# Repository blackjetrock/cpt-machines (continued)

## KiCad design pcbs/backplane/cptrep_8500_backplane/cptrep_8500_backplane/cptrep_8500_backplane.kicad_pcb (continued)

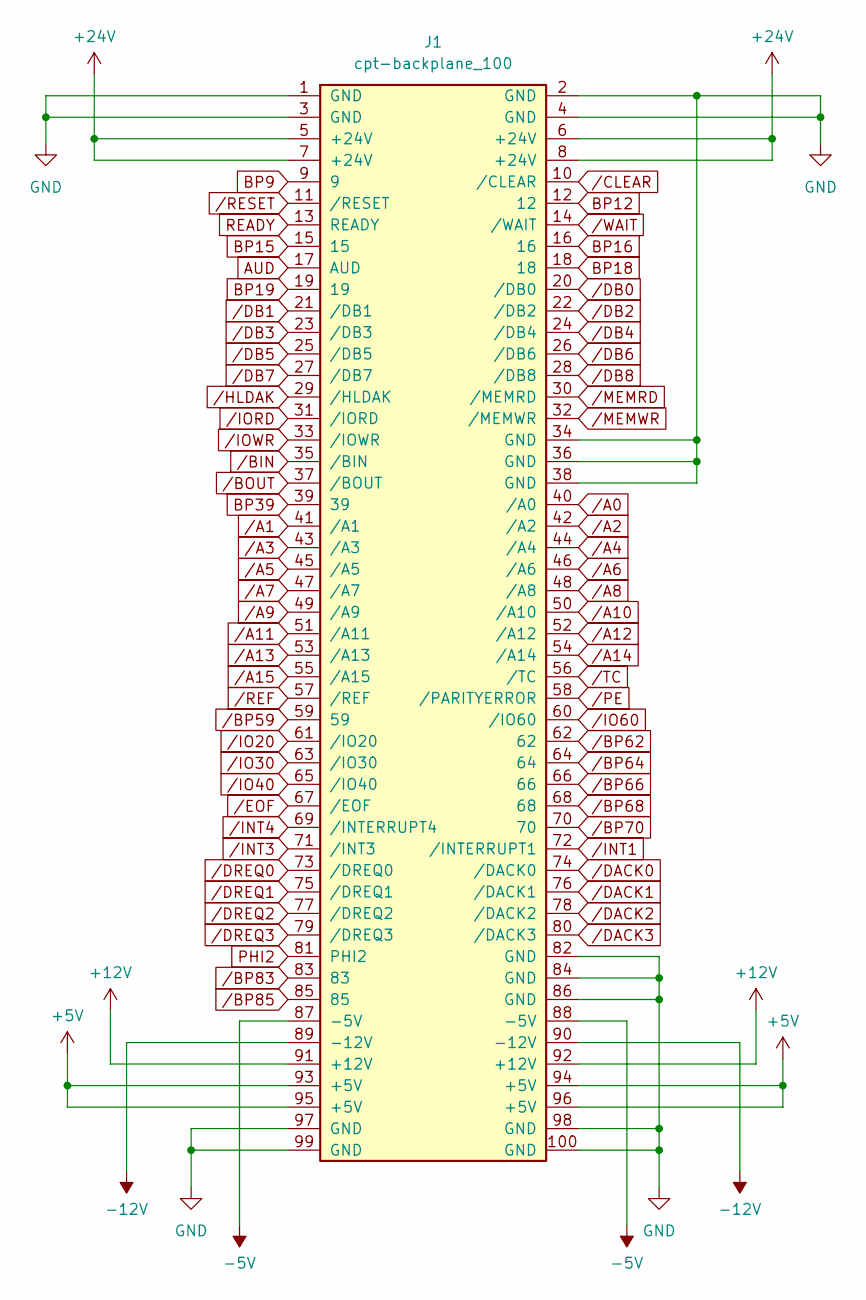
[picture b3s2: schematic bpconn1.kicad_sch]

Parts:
J1: cpt-backplane_100; cpt-8500-backplane-connector

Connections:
+5V: J1.93 (+5V), J1.94 (+5V), J1.95 (+5V), J1.96 (+5V); also elsewhere on the board
+12V: J1.91 (+12V), J1.92 (+12V); also elsewhere on the board
+24V: J1.5 (+24V), J1.6 (+24V), J1.7 (+24V), J1.8 (+24V); also elsewhere on the board
-5V: J1.87 (-5V), J1.88 (-5V); also elsewhere on the board
-12V: J1.89 (-12V), J1.90 (-12V); also elsewhere on the board
AUD: J1.17 (AUD); also elsewhere on the board
BP9: J1.9; also elsewhere on the board
BP12: J1.12; also elsewhere on the board
BP15: J1.15; also elsewhere on the board
BP16: J1.16; also elsewhere on the board
BP18: J1.18; also elsewhere on the board
BP19: J1.19; also elsewhere on the board
BP39: J1.39; also elsewhere on the board
GND: J1.1 (GND), J1.2 (GND), J1.3 (GND), J1.4 (GND), J1.34 (GND), J1.36 (GND), J1.38 (GND), J1.82 (GND), J1.84 (GND), J1.86 (GND), J1.97 (GND), J1.98 (GND), J1.99 (GND), J1.100 (GND); also elsewhere on the board
PHI2: J1.81 (PHI2); also elsewhere on the board
READY: J1.13 (READY); also elsewhere on the board
/A0: J1.40 (/A0); also elsewhere on the board
/A1: J1.41 (/A1); also elsewhere on the board
/A2: J1.42 (/A2); also elsewhere on the board
/A3: J1.43 (/A3); also elsewhere on the board
/A4: J1.44 (/A4); also elsewhere on the board
/A5: J1.45 (/A5); also elsewhere on the board
/A6: J1.46 (/A6); also elsewhere on the board
/A7: J1.47 (/A7); also elsewhere on the board
/A8: J1.48 (/A8); also elsewhere on the board
/A9: J1.49 (/A9); also elsewhere on the board
/A10: J1.50 (/A10); also elsewhere on the board
/A11: J1.51 (/A11); also elsewhere on the board
/A12: J1.52 (/A12); also elsewhere on the board
/A13: J1.53 (/A13); also elsewhere on the board
/A14: J1.54 (/A14); also elsewhere on the board
/A15: J1.55 (/A15); also elsewhere on the board
/BIN: J1.35 (/BIN); also elsewhere on the board
/BOUT: J1.37 (/BOUT); also elsewhere on the board
/BP59: J1.59; also elsewhere on the board
/BP62: J1.62; also elsewhere on the board
/BP64: J1.64; also elsewhere on the board
/BP66: J1.66; also elsewhere on the board
/BP68: J1.68; also elsewhere on the board
/BP70: J1.70; also elsewhere on the board
/BP83: J1.83; also elsewhere on the board
/BP85: J1.85; also elsewhere on the board
/CLEAR: J1.10 (/CLEAR); also elsewhere on the board
/DACK0: J1.74 (/DACK0); also elsewhere on the board
/DACK1: J1.76 (/DACK1); also elsewhere on the board
/DACK2: J1.78 (/DACK2); also elsewhere on the board
/DACK3: J1.80 (/DACK3); also elsewhere on the board
/DB0: J1.20 (/DB0); also elsewhere on the board
/DB1: J1.21 (/DB1); also elsewhere on the board
/DB2: J1.22 (/DB2); also elsewhere on the board
/DB3: J1.23 (/DB3); also elsewhere on the board
/DB4: J1.24 (/DB4); also elsewhere on the board
/DB5: J1.25 (/DB5); also elsewhere on the board
/DB6: J1.26 (/DB6); also elsewhere on the board
/DB7: J1.27 (/DB7); also elsewhere on the board
/DB8: J1.28 (/DB8); also elsewhere on the board
/DREQ0: J1.73 (/DREQ0); also elsewhere on the board
/DREQ1: J1.75 (/DREQ1); also elsewhere on the board
/DREQ2: J1.77 (/DREQ2); also elsewhere on the board
/DREQ3: J1.79 (/DREQ3); also elsewhere on the board
/EOF: J1.67 (/EOF); also elsewhere on the board
/HLDAK: J1.29 (/HLDAK); also elsewhere on the board
/INT1: J1.72 (/INTERRUPT1); also elsewhere on the board
/INT3: J1.71 (/INT3); also elsewhere on the board
/INT4: J1.69 (/INTERRUPT4); also elsewhere on the board
/IO20: J1.61 (/IO20); also elsewhere on the board
/IO30: J1.63 (/IO30); also elsewhere on the board
/IO40: J1.65 (/IO40); also elsewhere on the board
/IO60: J1.60 (/IO60); also elsewhere on the board
/IORD: J1.31 (/IORD); also elsewhere on the board
/IOWR: J1.33 (/IOWR); also elsewhere on the board
/MEMRD: J1.30 (/MEMRD); also elsewhere on the board
/MEMWR: J1.32 (/MEMWR); also elsewhere on the board
/PE: J1.58 (/PARITYERROR); also elsewhere on the board
/REF: J1.57 (/REF); also elsewhere on the board
/RESET: J1.11 (/RESET); also elsewhere on the board
/TC: J1.56 (/TC); also elsewhere on the board
/WAIT: J1.14 (/WAIT); also elsewhere on the board

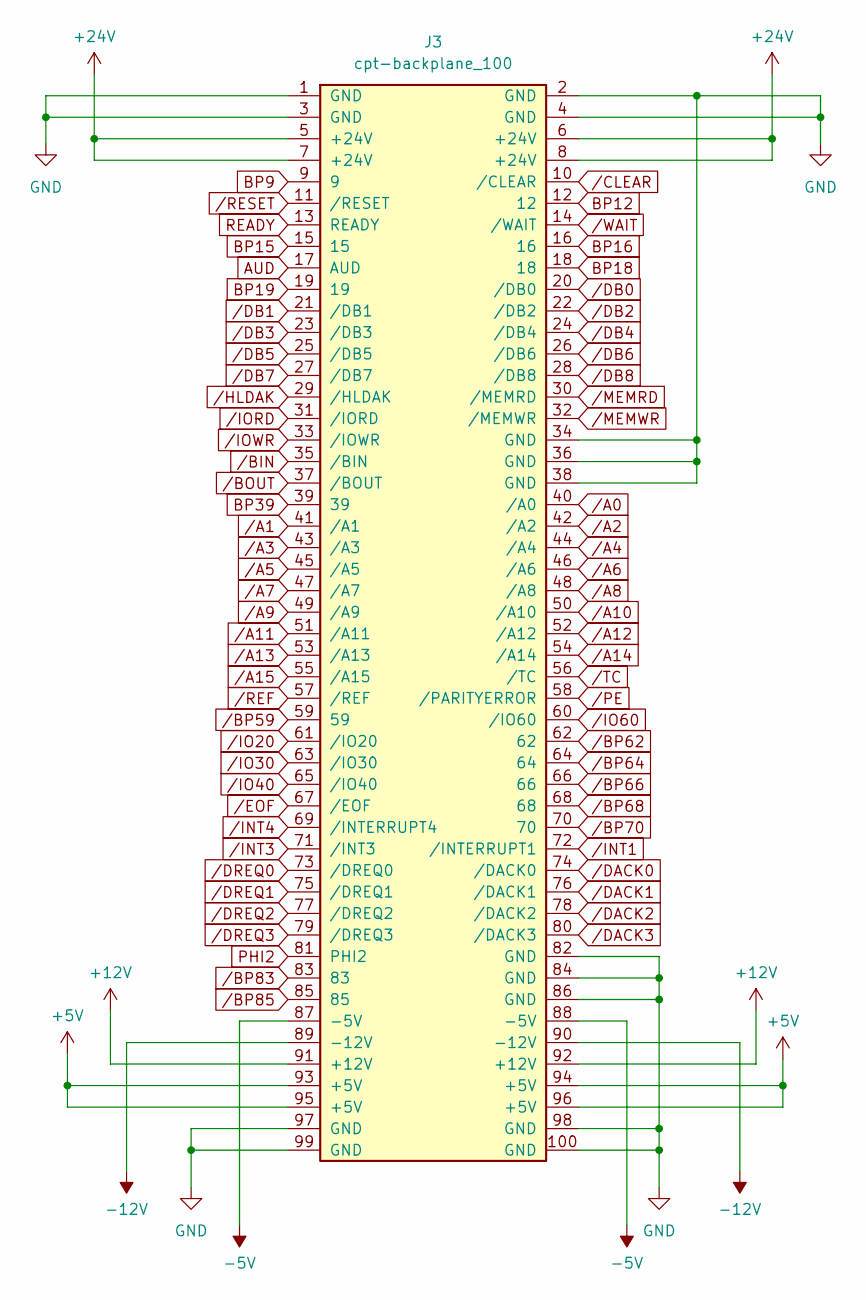
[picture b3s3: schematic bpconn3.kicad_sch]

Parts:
J3: cpt-backplane_100; cpt-8500-backplane-connector

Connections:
+5V: J3.93 (+5V), J3.94 (+5V), J3.95 (+5V), J3.96 (+5V); also elsewhere on the board
+12V: J3.91 (+12V), J3.92 (+12V); also elsewhere on the board
+24V: J3.5 (+24V), J3.6 (+24V), J3.7 (+24V), J3.8 (+24V); also elsewhere on the board
-5V: J3.87 (-5V), J3.88 (-5V); also elsewhere on the board
-12V: J3.89 (-12V), J3.90 (-12V); also elsewhere on the board
AUD: J3.17 (AUD); also elsewhere on the board
BP9: J3.9; also elsewhere on the board
BP12: J3.12; also elsewhere on the board
BP15: J3.15; also elsewhere on the board
BP16: J3.16; also elsewhere on the board
BP18: J3.18; also elsewhere on the board
BP19: J3.19; also elsewhere on the board
BP39: J3.39; also elsewhere on the board
GND: J3.1 (GND), J3.2 (GND), J3.3 (GND), J3.4 (GND), J3.34 (GND), J3.36 (GND), J3.38 (GND), J3.82 (GND), J3.84 (GND), J3.86 (GND), J3.97 (GND), J3.98 (GND), J3.99 (GND), J3.100 (GND); also elsewhere on the board
PHI2: J3.81 (PHI2); also elsewhere on the board
READY: J3.13 (READY); also elsewhere on the board
/A0: J3.40 (/A0); also elsewhere on the board
/A1: J3.41 (/A1); also elsewhere on the board
/A2: J3.42 (/A2); also elsewhere on the board
/A3: J3.43 (/A3); also elsewhere on the board
/A4: J3.44 (/A4); also elsewhere on the board
/A5: J3.45 (/A5); also elsewhere on the board
/A6: J3.46 (/A6); also elsewhere on the board
/A7: J3.47 (/A7); also elsewhere on the board
/A8: J3.48 (/A8); also elsewhere on the board
/A9: J3.49 (/A9); also elsewhere on the board
/A10: J3.50 (/A10); also elsewhere on the board
/A11: J3.51 (/A11); also elsewhere on the board
/A12: J3.52 (/A12); also elsewhere on the board
/A13: J3.53 (/A13); also elsewhere on the board
/A14: J3.54 (/A14); also elsewhere on the board
/A15: J3.55 (/A15); also elsewhere on the board
/BIN: J3.35 (/BIN); also elsewhere on the board
/BOUT: J3.37 (/BOUT); also elsewhere on the board
/BP59: J3.59; also elsewhere on the board
/BP62: J3.62; also elsewhere on the board
/BP64: J3.64; also elsewhere on the board
/BP66: J3.66; also elsewhere on the board
/BP68: J3.68; also elsewhere on the board
/BP70: J3.70; also elsewhere on the board
/BP83: J3.83; also elsewhere on the board
/BP85: J3.85; also elsewhere on the board
/CLEAR: J3.10 (/CLEAR); also elsewhere on the board
/DACK0: J3.74 (/DACK0); also elsewhere on the board
/DACK1: J3.76 (/DACK1); also elsewhere on the board
/DACK2: J3.78 (/DACK2); also elsewhere on the board
/DACK3: J3.80 (/DACK3); also elsewhere on the board
/DB0: J3.20 (/DB0); also elsewhere on the board
/DB1: J3.21 (/DB1); also elsewhere on the board
/DB2: J3.22 (/DB2); also elsewhere on the board
/DB3: J3.23 (/DB3); also elsewhere on the board
/DB4: J3.24 (/DB4); also elsewhere on the board
/DB5: J3.25 (/DB5); also elsewhere on the board
/DB6: J3.26 (/DB6); also elsewhere on the board
/DB7: J3.27 (/DB7); also elsewhere on the board
/DB8: J3.28 (/DB8); also elsewhere on the board
/DREQ0: J3.73 (/DREQ0); also elsewhere on the board
/DREQ1: J3.75 (/DREQ1); also elsewhere on the board
/DREQ2: J3.77 (/DREQ2); also elsewhere on the board
/DREQ3: J3.79 (/DREQ3); also elsewhere on the board
/EOF: J3.67 (/EOF); also elsewhere on the board
/HLDAK: J3.29 (/HLDAK); also elsewhere on the board
/INT1: J3.72 (/INTERRUPT1); also elsewhere on the board
/INT3: J3.71 (/INT3); also elsewhere on the board
/INT4: J3.69 (/INTERRUPT4); also elsewhere on the board
/IO20: J3.61 (/IO20); also elsewhere on the board
/IO30: J3.63 (/IO30); also elsewhere on the board
/IO40: J3.65 (/IO40); also elsewhere on the board
/IO60: J3.60 (/IO60); also elsewhere on the board
/IORD: J3.31 (/IORD); also elsewhere on the board
/IOWR: J3.33 (/IOWR); also elsewhere on the board
/MEMRD: J3.30 (/MEMRD); also elsewhere on the board
/MEMWR: J3.32 (/MEMWR); also elsewhere on the board
/PE: J3.58 (/PARITYERROR); also elsewhere on the board
/REF: J3.57 (/REF); also elsewhere on the board
/RESET: J3.11 (/RESET); also elsewhere on the board
/TC: J3.56 (/TC); also elsewhere on the board
/WAIT: J3.14 (/WAIT); also elsewhere on the board

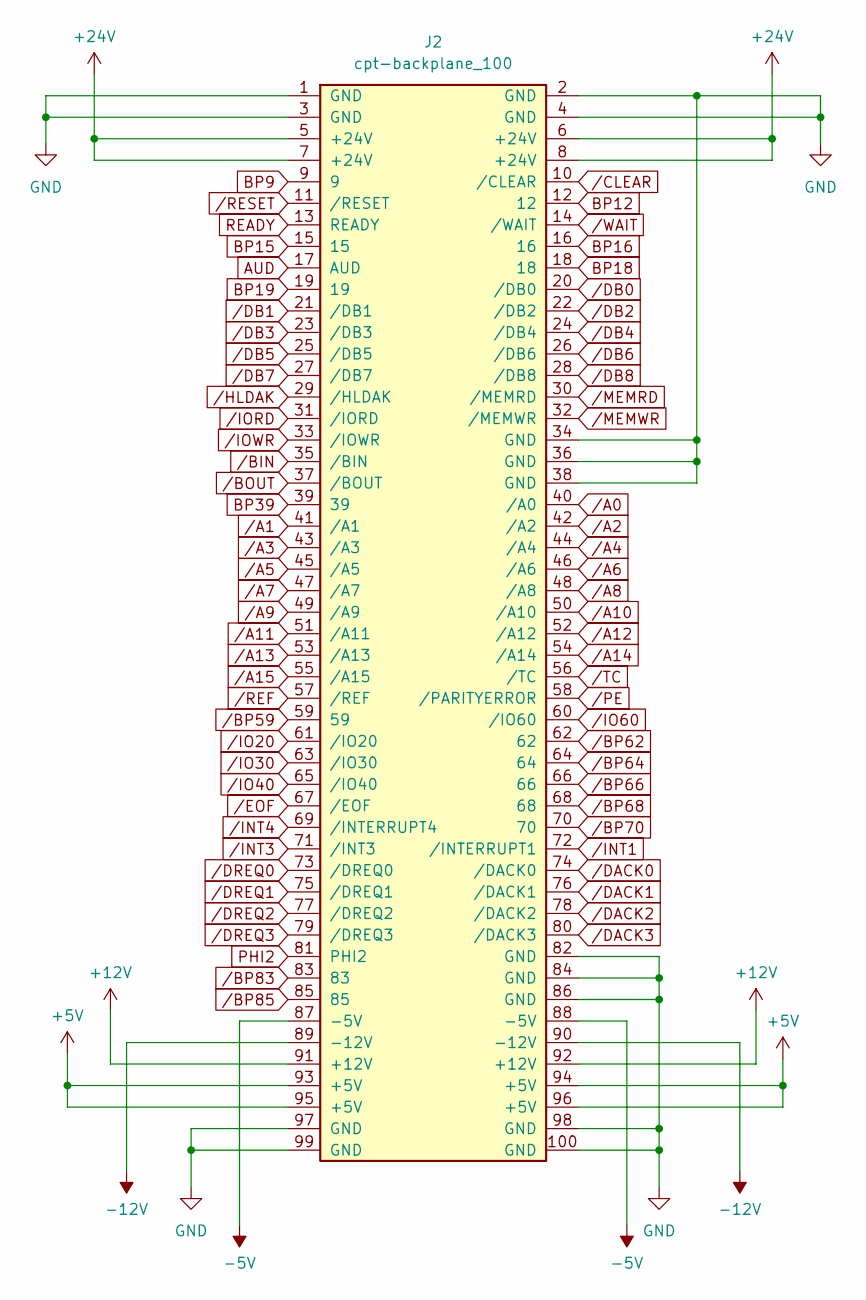
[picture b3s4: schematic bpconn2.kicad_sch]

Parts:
J2: cpt-backplane_100; cpt-8500-backplane-connector

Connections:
+5V: J2.93 (+5V), J2.94 (+5V), J2.95 (+5V), J2.96 (+5V); also elsewhere on the board
+12V: J2.91 (+12V), J2.92 (+12V); also elsewhere on the board
+24V: J2.5 (+24V), J2.6 (+24V), J2.7 (+24V), J2.8 (+24V); also elsewhere on the board
-5V: J2.87 (-5V), J2.88 (-5V); also elsewhere on the board
-12V: J2.89 (-12V), J2.90 (-12V); also elsewhere on the board
AUD: J2.17 (AUD); also elsewhere on the board
BP9: J2.9; also elsewhere on the board
BP12: J2.12; also elsewhere on the board
BP15: J2.15; also elsewhere on the board
BP16: J2.16; also elsewhere on the board
BP18: J2.18; also elsewhere on the board
BP19: J2.19; also elsewhere on the board
BP39: J2.39; also elsewhere on the board
GND: J2.1 (GND), J2.2 (GND), J2.3 (GND), J2.4 (GND), J2.34 (GND), J2.36 (GND), J2.38 (GND), J2.82 (GND), J2.84 (GND), J2.86 (GND), J2.97 (GND), J2.98 (GND), J2.99 (GND), J2.100 (GND); also elsewhere on the board
PHI2: J2.81 (PHI2); also elsewhere on the board
READY: J2.13 (READY); also elsewhere on the board
/A0: J2.40 (/A0); also elsewhere on the board
/A1: J2.41 (/A1); also elsewhere on the board
/A2: J2.42 (/A2); also elsewhere on the board
/A3: J2.43 (/A3); also elsewhere on the board
/A4: J2.44 (/A4); also elsewhere on the board
/A5: J2.45 (/A5); also elsewhere on the board
/A6: J2.46 (/A6); also elsewhere on the board
/A7: J2.47 (/A7); also elsewhere on the board
/A8: J2.48 (/A8); also elsewhere on the board
/A9: J2.49 (/A9); also elsewhere on the board
/A10: J2.50 (/A10); also elsewhere on the board
/A11: J2.51 (/A11); also elsewhere on the board
/A12: J2.52 (/A12); also elsewhere on the board
/A13: J2.53 (/A13); also elsewhere on the board
/A14: J2.54 (/A14); also elsewhere on the board
/A15: J2.55 (/A15); also elsewhere on the board
/BIN: J2.35 (/BIN); also elsewhere on the board
/BOUT: J2.37 (/BOUT); also elsewhere on the board
/BP59: J2.59; also elsewhere on the board
/BP62: J2.62; also elsewhere on the board
/BP64: J2.64; also elsewhere on the board
/BP66: J2.66; also elsewhere on the board
/BP68: J2.68; also elsewhere on the board
/BP70: J2.70; also elsewhere on the board
/BP83: J2.83; also elsewhere on the board
/BP85: J2.85; also elsewhere on the board
/CLEAR: J2.10 (/CLEAR); also elsewhere on the board
/DACK0: J2.74 (/DACK0); also elsewhere on the board
/DACK1: J2.76 (/DACK1); also elsewhere on the board
/DACK2: J2.78 (/DACK2); also elsewhere on the board
/DACK3: J2.80 (/DACK3); also elsewhere on the board
/DB0: J2.20 (/DB0); also elsewhere on the board
/DB1: J2.21 (/DB1); also elsewhere on the board
/DB2: J2.22 (/DB2); also elsewhere on the board
/DB3: J2.23 (/DB3); also elsewhere on the board
/DB4: J2.24 (/DB4); also elsewhere on the board
/DB5: J2.25 (/DB5); also elsewhere on the board
/DB6: J2.26 (/DB6); also elsewhere on the board
/DB7: J2.27 (/DB7); also elsewhere on the board
/DB8: J2.28 (/DB8); also elsewhere on the board
/DREQ0: J2.73 (/DREQ0); also elsewhere on the board
/DREQ1: J2.75 (/DREQ1); also elsewhere on the board
/DREQ2: J2.77 (/DREQ2); also elsewhere on the board
/DREQ3: J2.79 (/DREQ3); also elsewhere on the board
/EOF: J2.67 (/EOF); also elsewhere on the board
/HLDAK: J2.29 (/HLDAK); also elsewhere on the board
/INT1: J2.72 (/INTERRUPT1); also elsewhere on the board
/INT3: J2.71 (/INT3); also elsewhere on the board
/INT4: J2.69 (/INTERRUPT4); also elsewhere on the board
/IO20: J2.61 (/IO20); also elsewhere on the board
/IO30: J2.63 (/IO30); also elsewhere on the board
/IO40: J2.65 (/IO40); also elsewhere on the board
/IO60: J2.60 (/IO60); also elsewhere on the board
/IORD: J2.31 (/IORD); also elsewhere on the board
/IOWR: J2.33 (/IOWR); also elsewhere on the board
/MEMRD: J2.30 (/MEMRD); also elsewhere on the board
/MEMWR: J2.32 (/MEMWR); also elsewhere on the board
/PE: J2.58 (/PARITYERROR); also elsewhere on the board
/REF: J2.57 (/REF); also elsewhere on the board
/RESET: J2.11 (/RESET); also elsewhere on the board
/TC: J2.56 (/TC); also elsewhere on the board
/WAIT: J2.14 (/WAIT); also elsewhere on the board

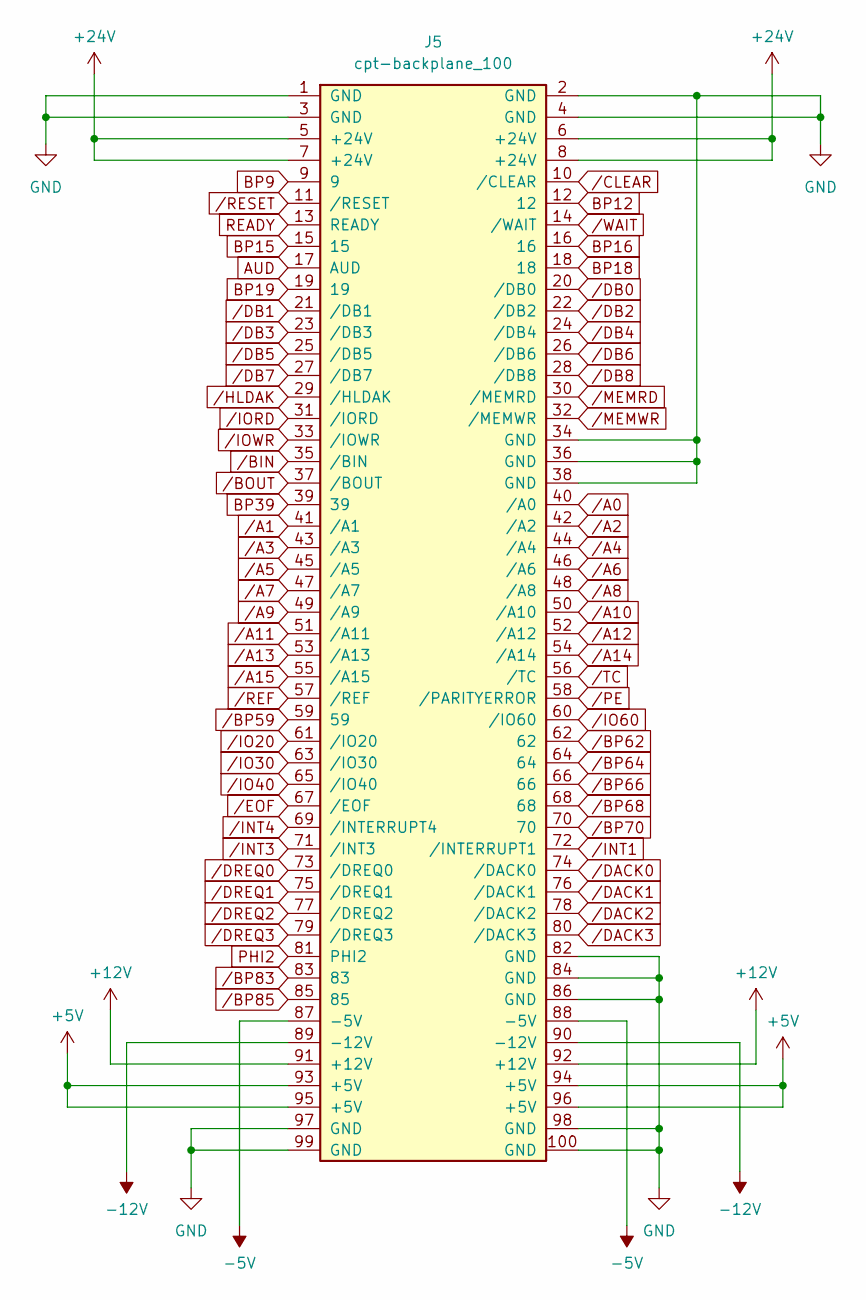
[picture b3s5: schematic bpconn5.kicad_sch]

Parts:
J5: cpt-backplane_100; cpt-8500-backplane-connector

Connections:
+5V: J5.93 (+5V), J5.94 (+5V), J5.95 (+5V), J5.96 (+5V); also elsewhere on the board
+12V: J5.91 (+12V), J5.92 (+12V); also elsewhere on the board
+24V: J5.5 (+24V), J5.6 (+24V), J5.7 (+24V), J5.8 (+24V); also elsewhere on the board
-5V: J5.87 (-5V), J5.88 (-5V); also elsewhere on the board
-12V: J5.89 (-12V), J5.90 (-12V); also elsewhere on the board
AUD: J5.17 (AUD); also elsewhere on the board
BP9: J5.9; also elsewhere on the board
BP12: J5.12; also elsewhere on the board
BP15: J5.15; also elsewhere on the board
BP16: J5.16; also elsewhere on the board
BP18: J5.18; also elsewhere on the board
BP19: J5.19; also elsewhere on the board
BP39: J5.39; also elsewhere on the board
GND: J5.1 (GND), J5.2 (GND), J5.3 (GND), J5.4 (GND), J5.34 (GND), J5.36 (GND), J5.38 (GND), J5.82 (GND), J5.84 (GND), J5.86 (GND), J5.97 (GND), J5.98 (GND), J5.99 (GND), J5.100 (GND); also elsewhere on the board
PHI2: J5.81 (PHI2); also elsewhere on the board
READY: J5.13 (READY); also elsewhere on the board
/A0: J5.40 (/A0); also elsewhere on the board
/A1: J5.41 (/A1); also elsewhere on the board
/A2: J5.42 (/A2); also elsewhere on the board
/A3: J5.43 (/A3); also elsewhere on the board
/A4: J5.44 (/A4); also elsewhere on the board
/A5: J5.45 (/A5); also elsewhere on the board
/A6: J5.46 (/A6); also elsewhere on the board
/A7: J5.47 (/A7); also elsewhere on the board
/A8: J5.48 (/A8); also elsewhere on the board
/A9: J5.49 (/A9); also elsewhere on the board
/A10: J5.50 (/A10); also elsewhere on the board
/A11: J5.51 (/A11); also elsewhere on the board
/A12: J5.52 (/A12); also elsewhere on the board
/A13: J5.53 (/A13); also elsewhere on the board
/A14: J5.54 (/A14); also elsewhere on the board
/A15: J5.55 (/A15); also elsewhere on the board
/BIN: J5.35 (/BIN); also elsewhere on the board
/BOUT: J5.37 (/BOUT); also elsewhere on the board
/BP59: J5.59; also elsewhere on the board
/BP62: J5.62; also elsewhere on the board
/BP64: J5.64; also elsewhere on the board
/BP66: J5.66; also elsewhere on the board
/BP68: J5.68; also elsewhere on the board
/BP70: J5.70; also elsewhere on the board
/BP83: J5.83; also elsewhere on the board
/BP85: J5.85; also elsewhere on the board
/CLEAR: J5.10 (/CLEAR); also elsewhere on the board
/DACK0: J5.74 (/DACK0); also elsewhere on the board
/DACK1: J5.76 (/DACK1); also elsewhere on the board
/DACK2: J5.78 (/DACK2); also elsewhere on the board
/DACK3: J5.80 (/DACK3); also elsewhere on the board
/DB0: J5.20 (/DB0); also elsewhere on the board
/DB1: J5.21 (/DB1); also elsewhere on the board
/DB2: J5.22 (/DB2); also elsewhere on the board
/DB3: J5.23 (/DB3); also elsewhere on the board
/DB4: J5.24 (/DB4); also elsewhere on the board
/DB5: J5.25 (/DB5); also elsewhere on the board
/DB6: J5.26 (/DB6); also elsewhere on the board
/DB7: J5.27 (/DB7); also elsewhere on the board
/DB8: J5.28 (/DB8); also elsewhere on the board
/DREQ0: J5.73 (/DREQ0); also elsewhere on the board
/DREQ1: J5.75 (/DREQ1); also elsewhere on the board
/DREQ2: J5.77 (/DREQ2); also elsewhere on the board
/DREQ3: J5.79 (/DREQ3); also elsewhere on the board
/EOF: J5.67 (/EOF); also elsewhere on the board
/HLDAK: J5.29 (/HLDAK); also elsewhere on the board
/INT1: J5.72 (/INTERRUPT1); also elsewhere on the board
/INT3: J5.71 (/INT3); also elsewhere on the board
/INT4: J5.69 (/INTERRUPT4); also elsewhere on the board
/IO20: J5.61 (/IO20); also elsewhere on the board
/IO30: J5.63 (/IO30); also elsewhere on the board
/IO40: J5.65 (/IO40); also elsewhere on the board
/IO60: J5.60 (/IO60); also elsewhere on the board
/IORD: J5.31 (/IORD); also elsewhere on the board
/IOWR: J5.33 (/IOWR); also elsewhere on the board
/MEMRD: J5.30 (/MEMRD); also elsewhere on the board
/MEMWR: J5.32 (/MEMWR); also elsewhere on the board
/PE: J5.58 (/PARITYERROR); also elsewhere on the board
/REF: J5.57 (/REF); also elsewhere on the board
/RESET: J5.11 (/RESET); also elsewhere on the board
/TC: J5.56 (/TC); also elsewhere on the board
/WAIT: J5.14 (/WAIT); also elsewhere on the board

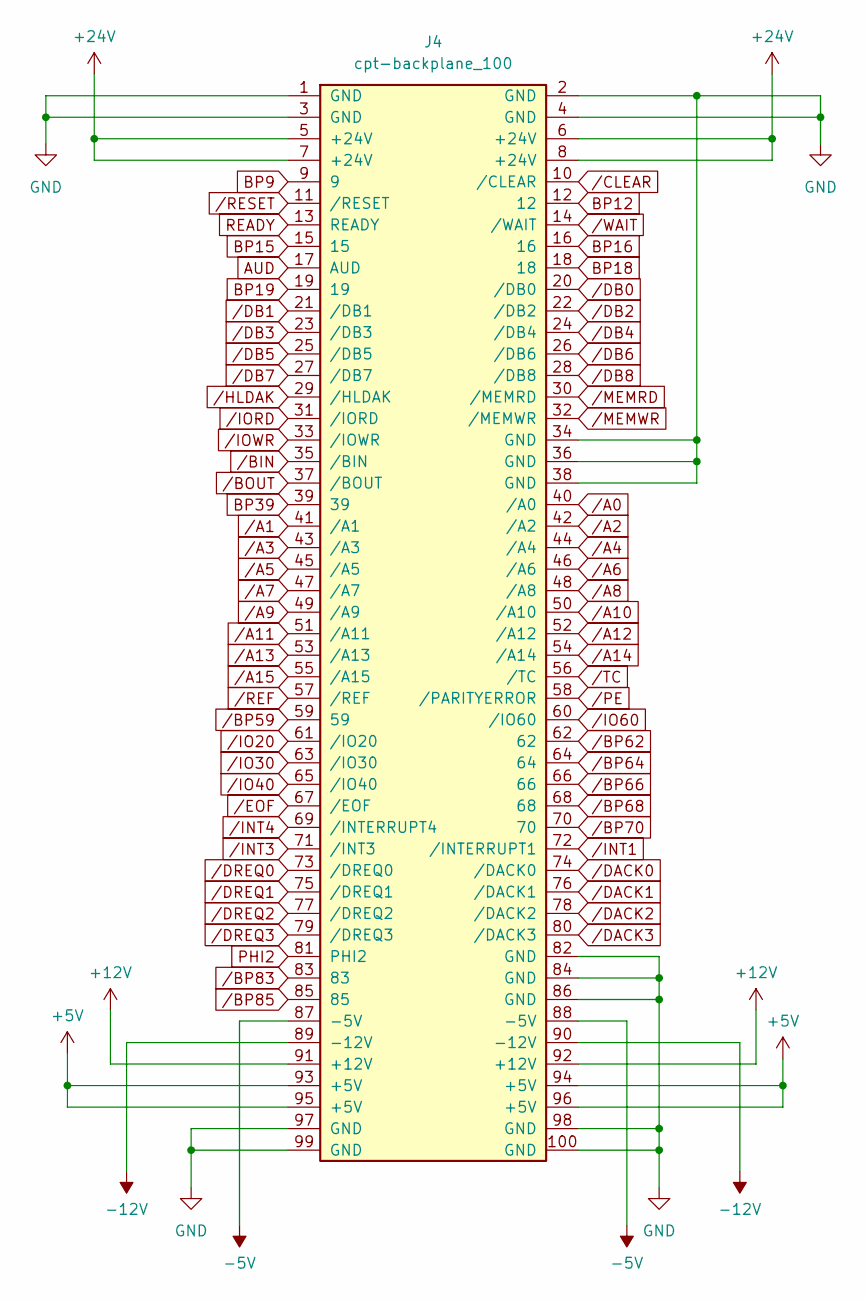
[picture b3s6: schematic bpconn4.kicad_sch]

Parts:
J4: cpt-backplane_100; cpt-8500-backplane-connector

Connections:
+5V: J4.93 (+5V), J4.94 (+5V), J4.95 (+5V), J4.96 (+5V); also elsewhere on the board
+12V: J4.91 (+12V), J4.92 (+12V); also elsewhere on the board
+24V: J4.5 (+24V), J4.6 (+24V), J4.7 (+24V), J4.8 (+24V); also elsewhere on the board
-5V: J4.87 (-5V), J4.88 (-5V); also elsewhere on the board
-12V: J4.89 (-12V), J4.90 (-12V); also elsewhere on the board
AUD: J4.17 (AUD); also elsewhere on the board
BP9: J4.9; also elsewhere on the board
BP12: J4.12; also elsewhere on the board
BP15: J4.15; also elsewhere on the board
BP16: J4.16; also elsewhere on the board
BP18: J4.18; also elsewhere on the board
BP19: J4.19; also elsewhere on the board
BP39: J4.39; also elsewhere on the board
GND: J4.1 (GND), J4.2 (GND), J4.3 (GND), J4.4 (GND), J4.34 (GND), J4.36 (GND), J4.38 (GND), J4.82 (GND), J4.84 (GND), J4.86 (GND), J4.97 (GND), J4.98 (GND), J4.99 (GND), J4.100 (GND); also elsewhere on the board
PHI2: J4.81 (PHI2); also elsewhere on the board
READY: J4.13 (READY); also elsewhere on the board
/A0: J4.40 (/A0); also elsewhere on the board
/A1: J4.41 (/A1); also elsewhere on the board
/A2: J4.42 (/A2); also elsewhere on the board
/A3: J4.43 (/A3); also elsewhere on the board
/A4: J4.44 (/A4); also elsewhere on the board
/A5: J4.45 (/A5); also elsewhere on the board
/A6: J4.46 (/A6); also elsewhere on the board
/A7: J4.47 (/A7); also elsewhere on the board
/A8: J4.48 (/A8); also elsewhere on the board
/A9: J4.49 (/A9); also elsewhere on the board
/A10: J4.50 (/A10); also elsewhere on the board
/A11: J4.51 (/A11); also elsewhere on the board
/A12: J4.52 (/A12); also elsewhere on the board
/A13: J4.53 (/A13); also elsewhere on the board
/A14: J4.54 (/A14); also elsewhere on the board
/A15: J4.55 (/A15); also elsewhere on the board
/BIN: J4.35 (/BIN); also elsewhere on the board
/BOUT: J4.37 (/BOUT); also elsewhere on the board
/BP59: J4.59; also elsewhere on the board
/BP62: J4.62; also elsewhere on the board
/BP64: J4.64; also elsewhere on the board
/BP66: J4.66; also elsewhere on the board
/BP68: J4.68; also elsewhere on the board
/BP70: J4.70; also elsewhere on the board
/BP83: J4.83; also elsewhere on the board
/BP85: J4.85; also elsewhere on the board
/CLEAR: J4.10 (/CLEAR); also elsewhere on the board
/DACK0: J4.74 (/DACK0); also elsewhere on the board
/DACK1: J4.76 (/DACK1); also elsewhere on the board
/DACK2: J4.78 (/DACK2); also elsewhere on the board
/DACK3: J4.80 (/DACK3); also elsewhere on the board
/DB0: J4.20 (/DB0); also elsewhere on the board
/DB1: J4.21 (/DB1); also elsewhere on the board
/DB2: J4.22 (/DB2); also elsewhere on the board
/DB3: J4.23 (/DB3); also elsewhere on the board
/DB4: J4.24 (/DB4); also elsewhere on the board
/DB5: J4.25 (/DB5); also elsewhere on the board
/DB6: J4.26 (/DB6); also elsewhere on the board
/DB7: J4.27 (/DB7); also elsewhere on the board
/DB8: J4.28 (/DB8); also elsewhere on the board
/DREQ0: J4.73 (/DREQ0); also elsewhere on the board
/DREQ1: J4.75 (/DREQ1); also elsewhere on the board
/DREQ2: J4.77 (/DREQ2); also elsewhere on the board
/DREQ3: J4.79 (/DREQ3); also elsewhere on the board
/EOF: J4.67 (/EOF); also elsewhere on the board
/HLDAK: J4.29 (/HLDAK); also elsewhere on the board
/INT1: J4.72 (/INTERRUPT1); also elsewhere on the board
/INT3: J4.71 (/INT3); also elsewhere on the board
/INT4: J4.69 (/INTERRUPT4); also elsewhere on the board
/IO20: J4.61 (/IO20); also elsewhere on the board
/IO30: J4.63 (/IO30); also elsewhere on the board
/IO40: J4.65 (/IO40); also elsewhere on the board
/IO60: J4.60 (/IO60); also elsewhere on the board
/IORD: J4.31 (/IORD); also elsewhere on the board
/IOWR: J4.33 (/IOWR); also elsewhere on the board
/MEMRD: J4.30 (/MEMRD); also elsewhere on the board
/MEMWR: J4.32 (/MEMWR); also elsewhere on the board
/PE: J4.58 (/PARITYERROR); also elsewhere on the board
/REF: J4.57 (/REF); also elsewhere on the board
/RESET: J4.11 (/RESET); also elsewhere on the board
/TC: J4.56 (/TC); also elsewhere on the board
/WAIT: J4.14 (/WAIT); also elsewhere on the board

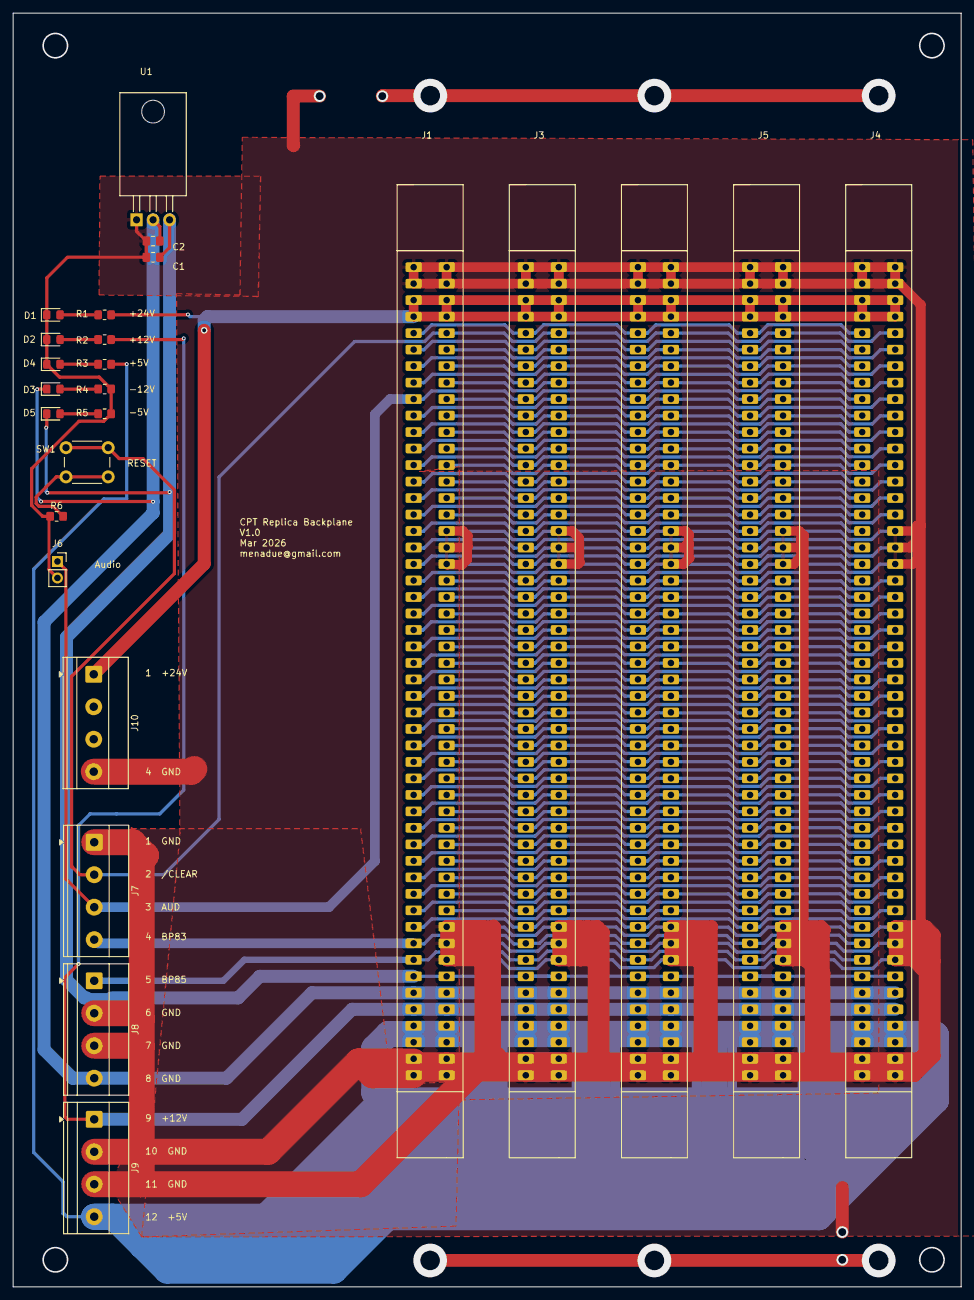
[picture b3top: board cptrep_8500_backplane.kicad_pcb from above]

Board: 2 copper layers, 146.0 x 196.2 mm, 25 parts (0 on the bottom side), 84 nets.

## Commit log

2026-02-28 "Update"
2026-03-28 Update README with CPT machine details
    Added detailed information about CPT word processor machines including the 4200, 8000, and 8500 models.
2026-03-28 Fix formatting issue in README.md
2026-03-30 Update README with backplane and diagnostic card details
    Added information about a diagnostic/debug card design.
2026-03-30 Add acknowledgements section to README
